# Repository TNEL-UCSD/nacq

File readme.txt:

Overview:
Design files for a electrophysiology (ephys) recording tailored for the clinic. Our system is based on Intan technologies (intantech.com). 

If any of the materials are used, please cite:

J. Hermiz, N. Rogers, E. Kaestner, M. Ganji, D. Cleary, J. Snider, D. Barba, S. Dayeh, E. Halgren, V. Gilja "A clinic compatible, open source electrophysiology system." 2016 38th Annual International Conference of the IEEE Engineering in Medicine and Biology Society (EMBC). IEEE, 2016.

Included in this system are:

-Power Isolator (nacq/pcbs/Isolation Board)
-> Provides isolated power to Intan headstages. Can support up to 256 channels.

-Easy Board (nacq/pcbs/Easy Board)
-> Adapter for isolator board to intan spi cables

-Flex Adapter (nacq/pcbs/Flex Adapter)
-> Adapter that accepts flat flex cables (FFC) and plugs into headstages (RHD2132 and RHD2164)

-NACQ Case (nacq/cases/nacq)
-> Enclosure for neural acquistion hardware (power isolator and RHD2000)

-Easy Board Case (nacq/cases/Easy Board)
-> 3D printed case

Flex Adapter Case (nacq/cases/Flex Adapter)
-> 3D printed case

Intan Headstage Cases (nacq/cases/Intan Headstages)
-> 3D printed cases for RHD2164

NACQ Software (nacq/software/nacq)
-> Software to acquire and record data. Runs only on Windows 7+ systems.

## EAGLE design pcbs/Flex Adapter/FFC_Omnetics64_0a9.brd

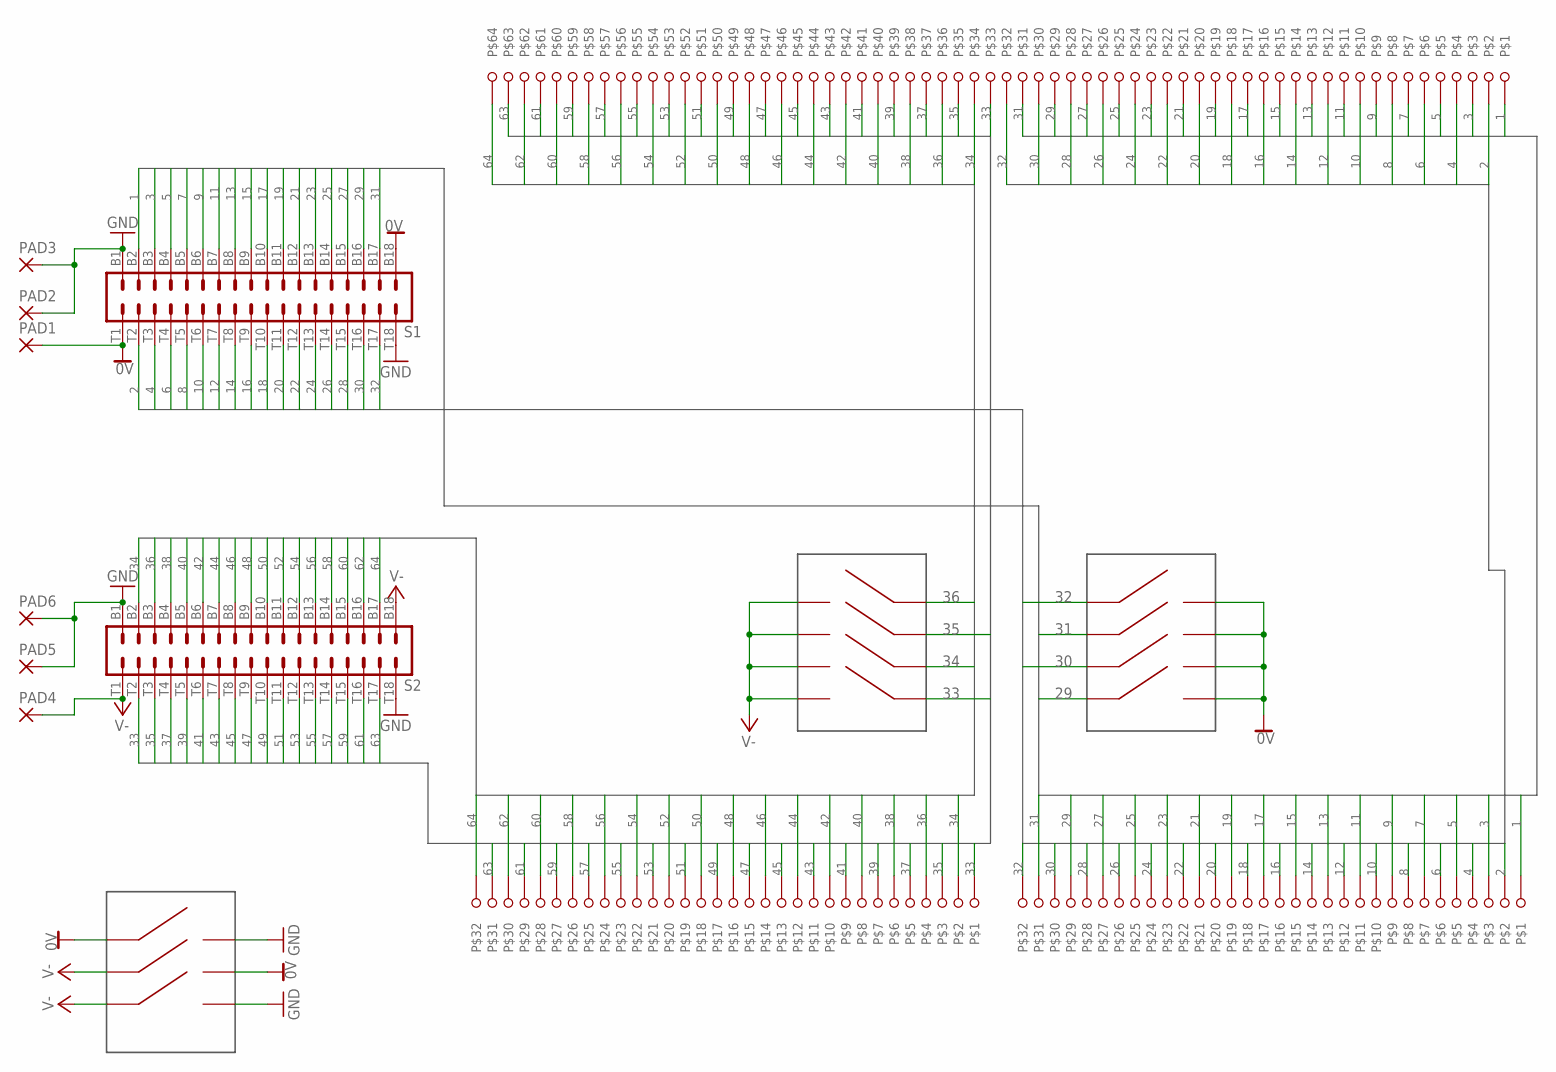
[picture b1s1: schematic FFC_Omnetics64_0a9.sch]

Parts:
PAD1, PAD2, PAD3, PAD4, PAD5, PAD6: 2,15/1,0
S1, S2: OMNETICS_A79024
U$1: OMRON64FFC-0.5MM; OMRONFFC64-0.5MM
U$2, U$3: OMRON32FFC-0.5MM; OMRON32
U$4, U$5: DIPSWITCH-4POS
U$6: DIPSWITCH-3POS

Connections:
0V: PAD1.1, S1.B18, S1.T1, U$4.P$5, U$4.P$6, U$4.P$7, U$4.P$8, U$6.P$1, U$6.P$5
1: S1.B2, U$1.P$64, U$3.P$32
2: S1.T2, U$1.P$63, U$3.P$31
3: S1.B3, U$1.P$62, U$3.P$30
4: S1.T3, U$1.P$61, U$3.P$29
5: S1.B4, U$1.P$60, U$3.P$28
6: S1.T4, U$1.P$59, U$3.P$27
7: S1.B5, U$1.P$58, U$3.P$26
8: S1.T5, U$1.P$57, U$3.P$25
9: S1.B6, U$1.P$56, U$3.P$24
10: S1.T6, U$1.P$55, U$3.P$23
11: S1.B7, U$1.P$54, U$3.P$22
12: S1.T7, U$1.P$53, U$3.P$21
13: S1.B8, U$1.P$52, U$3.P$20
14: S1.T8, U$1.P$51, U$3.P$19
15: S1.B9, U$1.P$50, U$3.P$18
16: S1.T9, U$1.P$49, U$3.P$17
17: S1.B10, U$1.P$48, U$3.P$16
18: S1.T10, U$1.P$47, U$3.P$15
19: S1.B11, U$1.P$46, U$3.P$14
20: S1.T11, U$1.P$45, U$3.P$13
21: S1.B12, U$1.P$44, U$3.P$12
22: S1.T12, U$1.P$43, U$3.P$11
23: S1.B13, U$1.P$42, U$3.P$10
24: S1.T13, U$1.P$41, U$3.P$9
25: S1.B14, U$1.P$40, U$3.P$8
26: S1.T14, U$1.P$39, U$3.P$7
27: S1.B15, U$1.P$38, U$3.P$6
28: S1.T15, U$1.P$37, U$3.P$5
29: S1.B16, U$1.P$36, U$3.P$4, U$4.P$4
30: S1.T16, U$1.P$35, U$3.P$3, U$4.P$3
31: S1.B17, U$1.P$34, U$3.P$2, U$4.P$2
32: S1.T17, U$1.P$33, U$3.P$1, U$4.P$1
33: S2.T2, U$1.P$32, U$2.P$32, U$5.P$4
34: S2.B2, U$1.P$31, U$2.P$31, U$5.P$3
35: S2.T3, U$1.P$30, U$2.P$30, U$5.P$2
36: S2.B3, U$1.P$29, U$2.P$29, U$5.P$1
37: S2.T4, U$1.P$28, U$2.P$28
38: S2.B4, U$1.P$27, U$2.P$27
39: S2.T5, U$1.P$26, U$2.P$26
40: S2.B5, U$1.P$25, U$2.P$25
41: S2.T6, U$1.P$24, U$2.P$24
42: S2.B6, U$1.P$23, U$2.P$23
43: S2.T7, U$1.P$22, U$2.P$22
44: S2.B7, U$1.P$21, U$2.P$21
45: S2.T8, U$1.P$20, U$2.P$20
46: S2.B8, U$1.P$19, U$2.P$19
47: S2.T9, U$1.P$18, U$2.P$18
48: S2.B9, U$1.P$17, U$2.P$17
49: S2.T10, U$1.P$16, U$2.P$16
50: S2.B10, U$1.P$15, U$2.P$15
51: S2.T11, U$1.P$14, U$2.P$14
52: S2.B11, U$1.P$13, U$2.P$13
53: S2.T12, U$1.P$12, U$2.P$12
54: S2.B12, U$1.P$11, U$2.P$11
55: S2.T13, U$1.P$10, U$2.P$10
56: S2.B13, U$1.P$9, U$2.P$9
57: S2.T14, U$1.P$8, U$2.P$8
58: S2.B14, U$1.P$7, U$2.P$7
59: S2.T15, U$1.P$6, U$2.P$6
60: S2.B15, U$1.P$5, U$2.P$5
61: S2.T16, U$1.P$4, U$2.P$4
62: S2.B16, U$1.P$3, U$2.P$3
63: S2.T17, U$1.P$2, U$2.P$2
64: S2.B17, U$1.P$1, U$2.P$1
GND: PAD2.1, PAD3.1, PAD5.1, PAD6.1, S1.B1, S1.T18, S2.B1, S2.T18, U$6.P$4, U$6.P$6
V-: PAD4.1, S2.B18, S2.T1, U$5.P$5, U$5.P$6, U$5.P$7, U$5.P$8, U$6.P$2, U$6.P$3

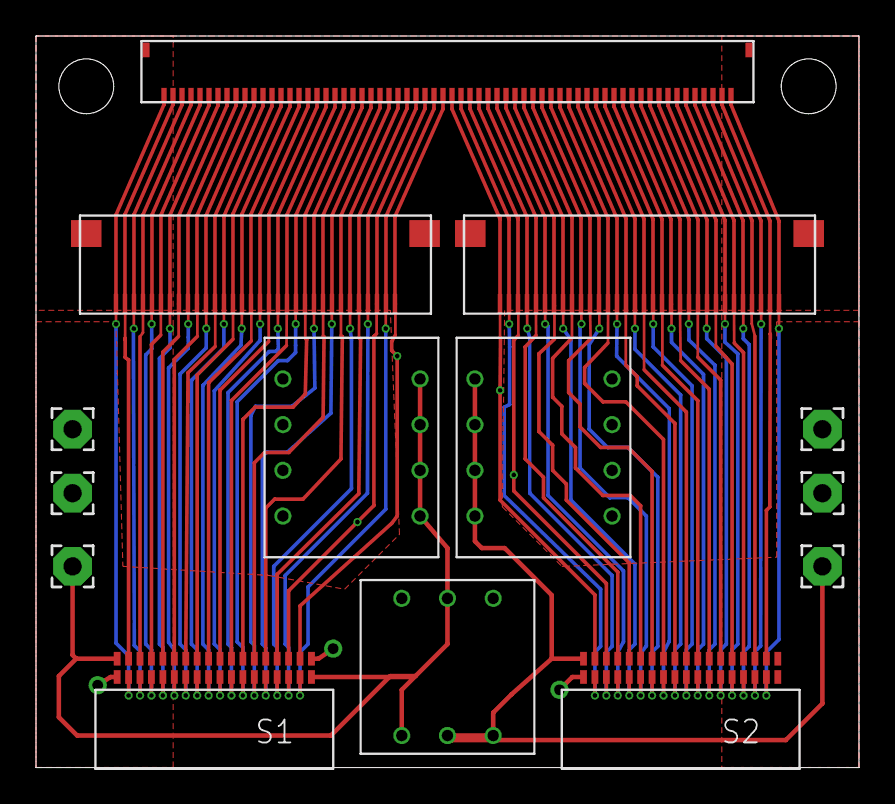
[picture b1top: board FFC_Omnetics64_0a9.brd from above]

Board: 4 copper layers, 45.7 x 40.6 mm, 14 parts (0 on the bottom side), 67 nets.

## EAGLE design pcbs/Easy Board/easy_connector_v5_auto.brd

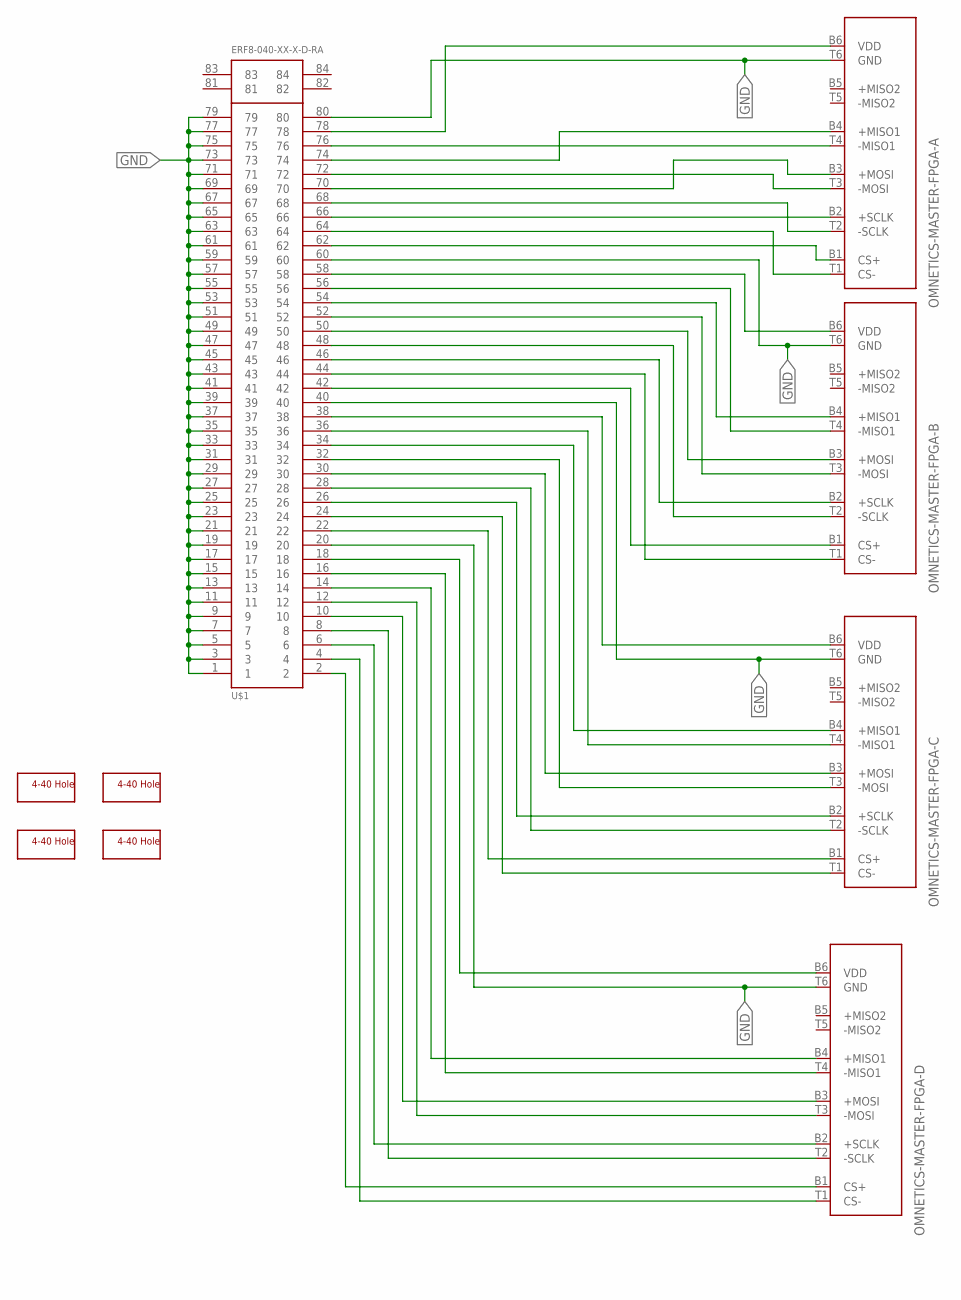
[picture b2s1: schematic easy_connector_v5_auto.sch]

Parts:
H1, H2, H3, H4: SCREW_HOLE_4-40
OMNETICS-MASTER-FPGA-A: OMNETIC-CONNECTOR; OMNETICS_PZN-12-AA-UPDATED
OMNETICS-MASTER-FPGA-B: OMNETIC-CONNECTOR; OMNETICS_PZN-12-AA-UPDATED
OMNETICS-MASTER-FPGA-C: OMNETIC-CONNECTOR; OMNETICS_PZN-12-AA-UPDATED
OMNETICS-MASTER-FPGA-D: OMNETIC-CONNECTOR; OMNETICS_PZN-12-AA-UPDATED
U$1: ERF8-040-XX-X-D-RA

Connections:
GND: OMNETICS-MASTER-FPGA-A.T6 (GND), OMNETICS-MASTER-FPGA-B.T6 (GND), OMNETICS-MASTER-FPGA-C.T6 (GND), OMNETICS-MASTER-FPGA-D.T6 (GND), U$1.1, U$1.3, U$1.5, U$1.7, U$1.9, U$1.11, U$1.13, U$1.15, U$1.17, U$1.19, U$1.20, U$1.21, U$1.23, U$1.25, U$1.27, U$1.29, U$1.31, U$1.33, U$1.35, U$1.37, U$1.39, U$1.40, U$1.41, U$1.43, U$1.45, U$1.47, U$1.49, U$1.51, U$1.53, U$1.55, U$1.57, U$1.59, U$1.60, U$1.61, U$1.63, U$1.65, U$1.67, U$1.69, U$1.71, U$1.73, U$1.75, U$1.77, U$1.79, U$1.80
MISO1_N: OMNETICS-MASTER-FPGA-A.T4 (-MISO1), U$1.76
MISO1_P: OMNETICS-MASTER-FPGA-A.B4 (+MISO1), U$1.74
unnamed: OMNETICS-MASTER-FPGA-A.T3 (-MOSI), U$1.72
unnamed: OMNETICS-MASTER-FPGA-A.B3 (+MOSI), U$1.70
unnamed: OMNETICS-MASTER-FPGA-A.T2 (-SCLK), U$1.68
unnamed: OMNETICS-MASTER-FPGA-A.B2 (+SCLK), U$1.66
unnamed: OMNETICS-MASTER-FPGA-A.T1 (CS-), U$1.64
unnamed: OMNETICS-MASTER-FPGA-A.B1 (CS+), U$1.62
unnamed: OMNETICS-MASTER-FPGA-B.T4 (-MISO1), U$1.56
unnamed: OMNETICS-MASTER-FPGA-B.B4 (+MISO1), U$1.54
unnamed: OMNETICS-MASTER-FPGA-B.T3 (-MOSI), U$1.52
unnamed: OMNETICS-MASTER-FPGA-B.B3 (+MOSI), U$1.50
unnamed: OMNETICS-MASTER-FPGA-B.T2 (-SCLK), U$1.48
unnamed: OMNETICS-MASTER-FPGA-B.B2 (+SCLK), U$1.46
unnamed: OMNETICS-MASTER-FPGA-B.T1 (CS-), U$1.44
unnamed: OMNETICS-MASTER-FPGA-B.B1 (CS+), U$1.42
unnamed: OMNETICS-MASTER-FPGA-C.T4 (-MISO1), U$1.36
unnamed: OMNETICS-MASTER-FPGA-C.B4 (+MISO1), U$1.34
unnamed: OMNETICS-MASTER-FPGA-C.T3 (-MOSI), U$1.32
unnamed: OMNETICS-MASTER-FPGA-C.B3 (+MOSI), U$1.30
unnamed: OMNETICS-MASTER-FPGA-C.T2 (-SCLK), U$1.28
unnamed: OMNETICS-MASTER-FPGA-C.B2 (+SCLK), U$1.26
unnamed: OMNETICS-MASTER-FPGA-C.T1 (CS-), U$1.24
unnamed: OMNETICS-MASTER-FPGA-C.B1 (CS+), U$1.22
unnamed: OMNETICS-MASTER-FPGA-D.T4 (-MISO1), U$1.16
unnamed: OMNETICS-MASTER-FPGA-D.B4 (+MISO1), U$1.14
unnamed: OMNETICS-MASTER-FPGA-D.T3 (-MOSI), U$1.12
unnamed: OMNETICS-MASTER-FPGA-D.B3 (+MOSI), U$1.10
unnamed: OMNETICS-MASTER-FPGA-D.T2 (-SCLK), U$1.8
unnamed: OMNETICS-MASTER-FPGA-D.B2 (+SCLK), U$1.6
unnamed: OMNETICS-MASTER-FPGA-D.T1 (CS-), U$1.4
unnamed: OMNETICS-MASTER-FPGA-D.B1 (CS+), U$1.2
VDD-A: OMNETICS-MASTER-FPGA-A.B6 (VDD), U$1.78
VDD-B: OMNETICS-MASTER-FPGA-B.B6 (VDD), U$1.58
VDD-C: OMNETICS-MASTER-FPGA-C.B6 (VDD), U$1.38
VDD-D: OMNETICS-MASTER-FPGA-D.B6 (VDD), U$1.18

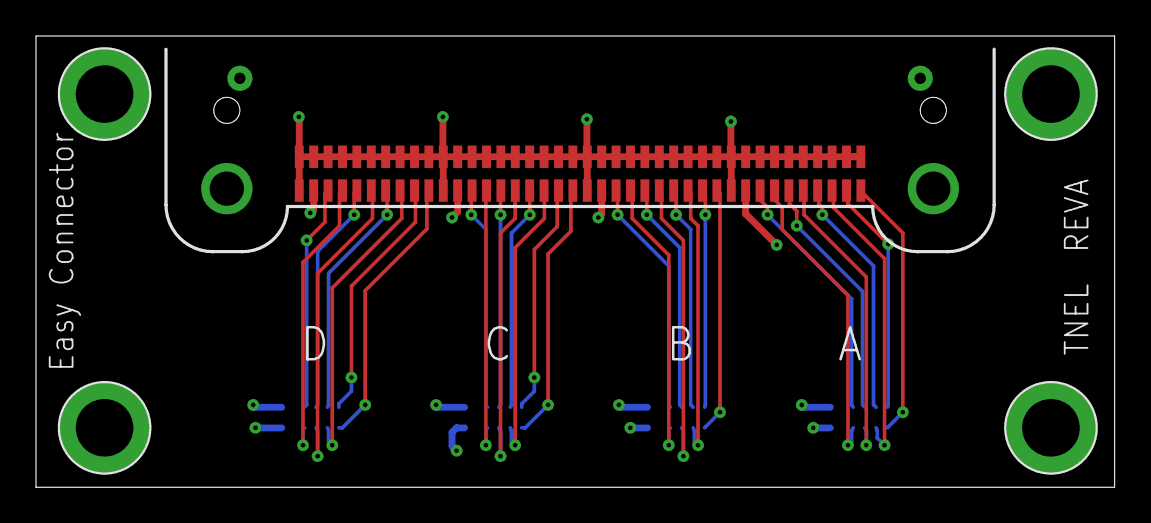
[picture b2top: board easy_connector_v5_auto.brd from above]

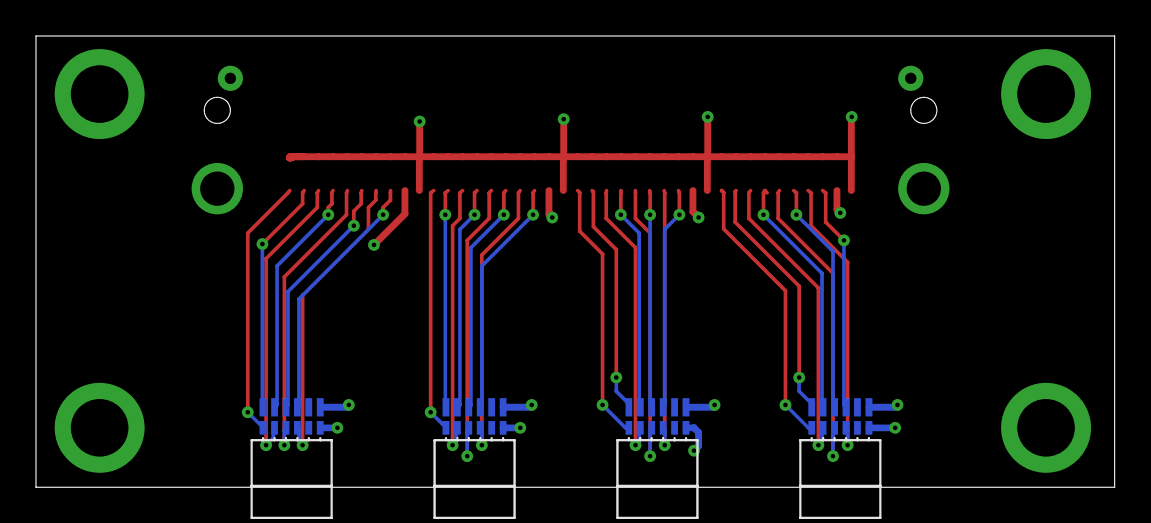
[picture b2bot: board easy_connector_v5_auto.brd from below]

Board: 4 copper layers, 59.9 x 25.1 mm, 9 parts (4 on the bottom side), 37 nets.

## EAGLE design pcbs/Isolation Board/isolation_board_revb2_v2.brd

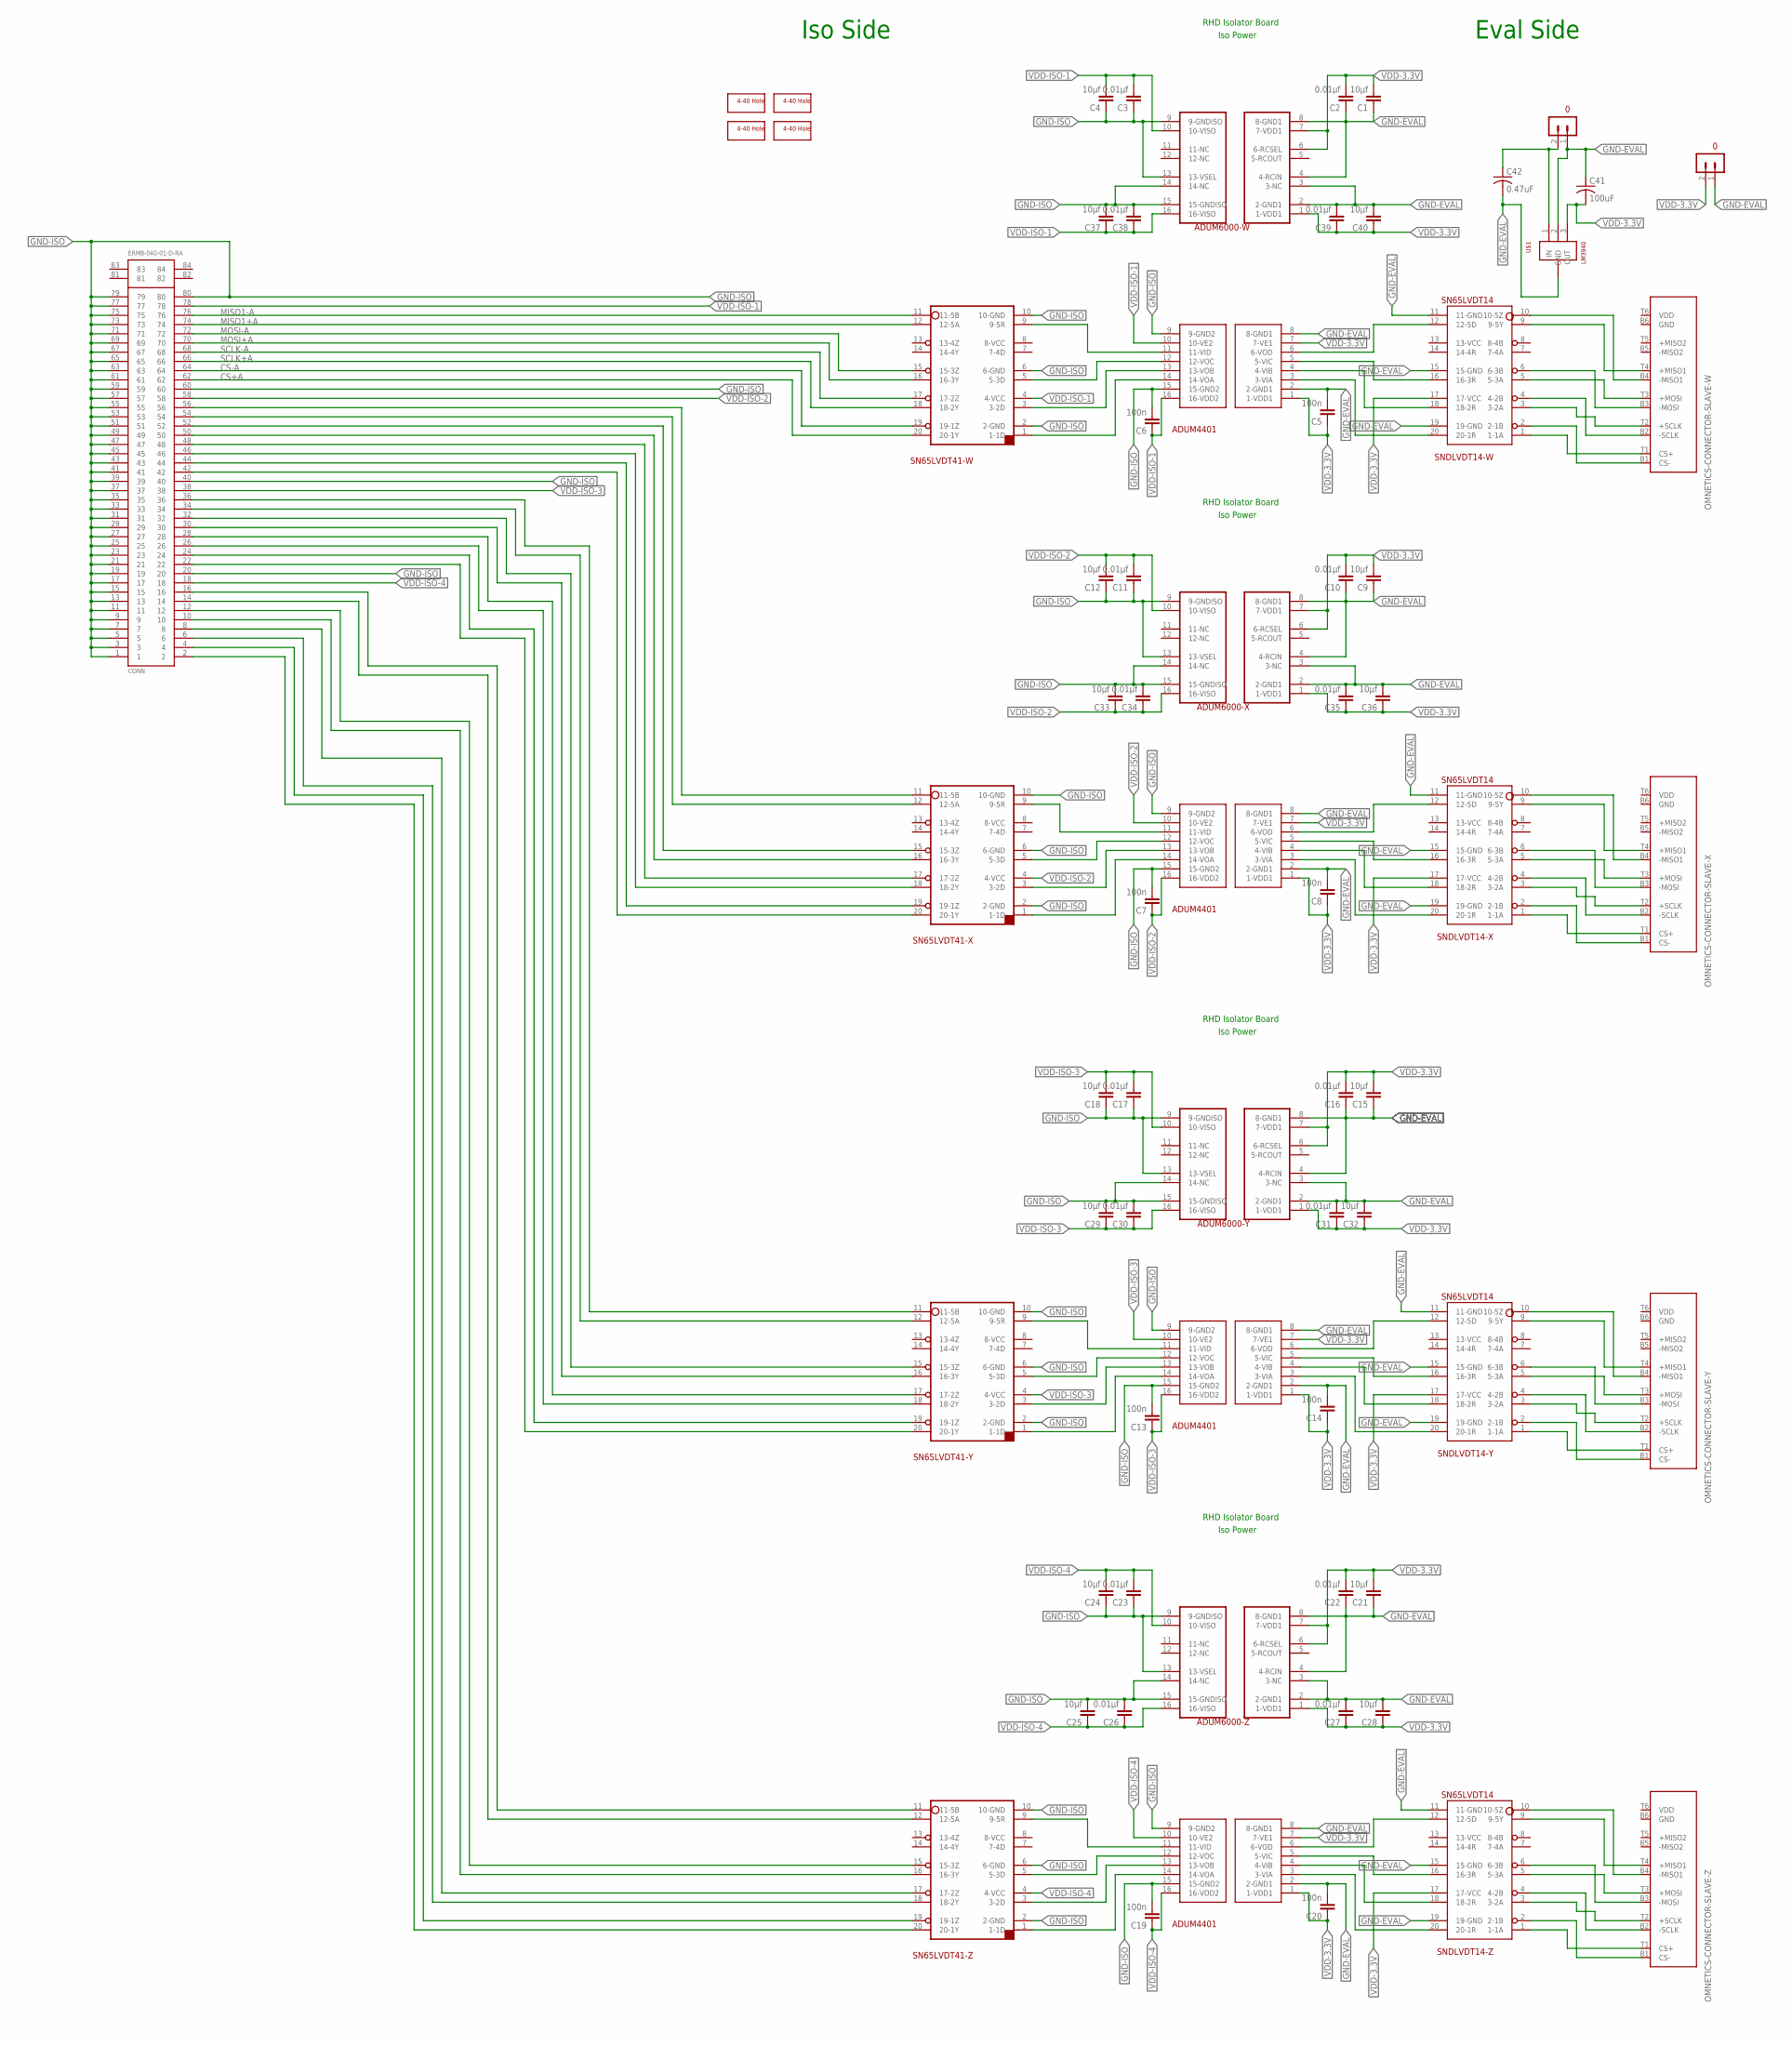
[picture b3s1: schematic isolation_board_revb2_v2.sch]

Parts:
ADUM4401-W, ADUM4401-X, ADUM4401-Y, ADUM4401-Z: ADUM4401; SOIC16R
ADUM6000-W, ADUM6000-X, ADUM6000-Y, ADUM6000-Z: ADUM6000; SOIC16R; MPN ADUM6000ARWZ
C1, C4, C9, C12, C15, C18, C21, C24, C25, C28, C29, C32, C33, C36, C37, C40: 10µf; 0805
C2, C3, C10, C11, C16, C17, C22, C23, C26, C27, C30, C31, C34, C35, C38, C39: 0.01µf; 0805
C5, C6, C7, C8, C13, C14, C19, C20: 100n; 0805
C41: 100uF; C1206
C42: 0.47uF; C0603
CONN: ERM8-040-01-D-RA
H1, H2, H3, H4: SCREW_HOLE_4-40
OMNETICS-CONNECTOR-SLAVE-W: OMNETICS-CONNECTOR-SLAVE-SIDE; OMNETICS_PZN-12-AA-UPDATED
OMNETICS-CONNECTOR-SLAVE-X: OMNETICS-CONNECTOR-SLAVE-SIDE; OMNETICS_PZN-12-AA-UPDATED
OMNETICS-CONNECTOR-SLAVE-Y: OMNETICS-CONNECTOR-SLAVE-SIDE; OMNETICS_PZN-12-AA-UPDATED
OMNETICS-CONNECTOR-SLAVE-Z: OMNETICS-CONNECTOR-SLAVE-SIDE; OMNETICS_PZN-12-AA-UPDATED
S1: TERMINAL_BLOCK_2-3.5MM-5V; TERMINAL_BLOCK_3.5MM_2_5V
S2: TERMINAL_BLOCK_2-3.5MM-3.3V; TERMINAL_BLOCK_3.5MM_2_3.3V
SN65LVDT41-W, SN65LVDT41-X, SN65LVDT41-Y, SN65LVDT41-Z: SN65LVDT41; SN65LVDT41-UPDATED
SNDLVDT14-W, SNDLVDT14-X, SNDLVDT14-Y, SNDLVDT14-Z: SN65LVDT14; SN65LDVT14
U$1: LM3940; SOT223

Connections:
CS+A: CONN.62, SN65LVDT41-W.20 (20-1Y)
CS-A: CONN.64, SN65LVDT41-W.19 (19-1Z)
GND-EVAL: ADUM4401-W.2 (2-GND1), ADUM4401-W.8 (8-GND1), ADUM4401-X.2 (2-GND1), ADUM4401-X.8 (8-GND1), ADUM4401-Y.2 (2-GND1), ADUM4401-Y.8 (8-GND1), ADUM4401-Z.2 (2-GND1), ADUM4401-Z.8 (8-GND1), ADUM6000-W.2 (2-GND1), ADUM6000-W.3 (3-NC), ADUM6000-W.4 (4-RCIN), ADUM6000-W.8 (8-GND1), ADUM6000-X.2 (2-GND1), ADUM6000-X.3 (3-NC), ADUM6000-X.4 (4-RCIN), ADUM6000-X.8 (8-GND1), ADUM6000-Y.2 (2-GND1), ADUM6000-Y.3 (3-NC), ADUM6000-Y.4 (4-RCIN), ADUM6000-Y.8 (8-GND1), ADUM6000-Z.2 (2-GND1), ADUM6000-Z.3 (3-NC), ADUM6000-Z.4 (4-RCIN), ADUM6000-Z.8 (8-GND1), C1.1, C2.1, C5.2, C8.2, C9.1, C10.1, C14.2, C15.1, C16.1, C20.2, C21.1, C22.1, C27.2, C28.2, C31.2, C32.2, C35.2, C36.2, C39.2, C40.2, C41.1, C42.2, S1.1 (0), S2.1 (0), SNDLVDT14-W.11 (11-GND), SNDLVDT14-W.15 (15-GND), SNDLVDT14-W.19 (19-GND), SNDLVDT14-X.11 (11-GND), SNDLVDT14-X.15 (15-GND), SNDLVDT14-X.19 (19-GND), SNDLVDT14-Y.11 (11-GND), SNDLVDT14-Y.15 (15-GND), SNDLVDT14-Y.19 (19-GND), SNDLVDT14-Z.11 (11-GND), SNDLVDT14-Z.15 (15-GND), SNDLVDT14-Z.19 (19-GND), U$1.2 (GND), U$1.4 (GND_T)
GND-ISO: ADUM4401-W.9 (9-GND2), ADUM4401-W.15 (15-GND2), ADUM4401-X.9 (9-GND2), ADUM4401-X.15 (15-GND2), ADUM4401-Y.9 (9-GND2), ADUM4401-Y.15 (15-GND2), ADUM4401-Z.9 (9-GND2), ADUM4401-Z.15 (15-GND2), ADUM6000-W.9 (9-GNDISO), ADUM6000-W.13 (13-VSEL), ADUM6000-W.14 (14-NC), ADUM6000-W.15 (15-GNDISO), ADUM6000-X.9 (9-GNDISO), ADUM6000-X.13 (13-VSEL), ADUM6000-X.14 (14-NC), ADUM6000-X.15 (15-GNDISO), ADUM6000-Y.9 (9-GNDISO), ADUM6000-Y.13 (13-VSEL), ADUM6000-Y.14 (14-NC), ADUM6000-Y.15 (15-GNDISO), ADUM6000-Z.9 (9-GNDISO), ADUM6000-Z.13 (13-VSEL), ADUM6000-Z.14 (14-NC), ADUM6000-Z.15 (15-GNDISO), C3.1, C4.1, C6.2, C7.2, C11.1, C12.1, C13.2, C17.1, C18.1, C19.2, C23.1, C24.1, C25.2, C26.2, C29.2, C30.2, C33.2, C34.2, C37.2, C38.2, CONN.1, CONN.3, CONN.5, CONN.7, CONN.9, CONN.11, CONN.13, CONN.15, CONN.17, CONN.19, CONN.20, CONN.21, CONN.23, CONN.25, CONN.27, CONN.29, CONN.31, CONN.33, CONN.35, CONN.37, CONN.39, CONN.40, CONN.41, CONN.43, CONN.45, CONN.47, CONN.49, CONN.51, CONN.53, CONN.55, CONN.57, CONN.59, CONN.60, CONN.61, CONN.63, CONN.65, CONN.67, CONN.69, CONN.71, CONN.73, CONN.75, CONN.77, CONN.79, CONN.80, SN65LVDT41-W.2 (2-GND), SN65LVDT41-W.6 (6-GND), SN65LVDT41-W.10 (10-GND), SN65LVDT41-X.2 (2-GND), SN65LVDT41-X.6 (6-GND), SN65LVDT41-X.10 (10-GND), SN65LVDT41-Y.2 (2-GND), SN65LVDT41-Y.6 (6-GND), SN65LVDT41-Y.10 (10-GND), SN65LVDT41-Z.2 (2-GND), SN65LVDT41-Z.6 (6-GND), SN65LVDT41-Z.10 (10-GND)
MISO1+A: CONN.74, SN65LVDT41-W.12 (12-5A)
MISO1-A: CONN.76, SN65LVDT41-W.11 (11-5B)
MOSI+A: CONN.70, SN65LVDT41-W.16 (16-3Y)
MOSI-A: CONN.72, SN65LVDT41-W.15 (15-3Z)
unnamed: ADUM4401-W.12 (12-VOC), SN65LVDT41-W.5 (5-3D)
unnamed: OMNETICS-CONNECTOR-SLAVE-W.B1 (CS-), SNDLVDT14-W.2 (2-1B)
unnamed: ADUM4401-W.11 (11-VID), SN65LVDT41-W.9 (9-5R)
unnamed: ADUM4401-W.13 (13-VOB), SN65LVDT41-W.3 (3-2D)
unnamed: ADUM4401-W.5 (5-VIC), SNDLVDT14-W.16 (16-3R)
unnamed: CONN.56, SN65LVDT41-X.11 (11-5B)
unnamed: ADUM4401-W.14 (14-VOA), SN65LVDT41-W.1 (1-1D)
unnamed: ADUM4401-W.3 (3-VIA), SNDLVDT14-W.20 (20-1R)
unnamed: ADUM4401-W.4 (4-VIB), SNDLVDT14-W.18 (18-2R)
unnamed: CONN.54, SN65LVDT41-X.12 (12-5A)
unnamed: ADUM4401-W.6 (6-VOD), SNDLVDT14-W.12 (12-5D)
unnamed: OMNETICS-CONNECTOR-SLAVE-W.T1 (CS+), SNDLVDT14-W.1 (1-1A)
unnamed: CONN.52, SN65LVDT41-X.15 (15-3Z)
unnamed: CONN.50, SN65LVDT41-X.16 (16-3Y)
unnamed: OMNETICS-CONNECTOR-SLAVE-W.T2 (+SCLK), SNDLVDT14-W.3 (3-2A)
unnamed: OMNETICS-CONNECTOR-SLAVE-W.B2 (-SCLK), SNDLVDT14-W.4 (4-2B)
unnamed: CONN.48, SN65LVDT41-X.17 (17-2Z)
unnamed: CONN.46, SN65LVDT41-X.18 (18-2Y)
unnamed: CONN.44, SN65LVDT41-X.19 (19-1Z)
unnamed: CONN.42, SN65LVDT41-X.20 (20-1Y)
unnamed: OMNETICS-CONNECTOR-SLAVE-X.T2 (+SCLK), SNDLVDT14-X.3 (3-2A)
unnamed: OMNETICS-CONNECTOR-SLAVE-X.B2 (-SCLK), SNDLVDT14-X.4 (4-2B)
unnamed: OMNETICS-CONNECTOR-SLAVE-X.T3 (+MOSI), SNDLVDT14-X.5 (5-3A)
unnamed: OMNETICS-CONNECTOR-SLAVE-X.B3 (-MOSI), SNDLVDT14-X.6 (6-3B)
unnamed: OMNETICS-CONNECTOR-SLAVE-X.T4 (+MISO1), SNDLVDT14-X.9 (9-5Y)
unnamed: OMNETICS-CONNECTOR-SLAVE-X.B4 (-MISO1), SNDLVDT14-X.10 (10-5Z)
unnamed: CONN.36, SN65LVDT41-Y.11 (11-5B)
unnamed: CONN.34, SN65LVDT41-Y.12 (12-5A)
unnamed: ADUM4401-X.14 (14-VOA), SN65LVDT41-X.1 (1-1D)
unnamed: CONN.32, SN65LVDT41-Y.15 (15-3Z)
unnamed: CONN.30, SN65LVDT41-Y.16 (16-3Y)
unnamed: ADUM4401-X.11 (11-VID), SN65LVDT41-X.9 (9-5R)
unnamed: CONN.28, SN65LVDT41-Y.17 (17-2Z)
unnamed: CONN.26, SN65LVDT41-Y.18 (18-2Y)
unnamed: C42.1, S1.2 (1), U$1.1 (IN)
unnamed: ADUM4401-X.6 (6-VOD), SNDLVDT14-X.12 (12-5D)
unnamed: OMNETICS-CONNECTOR-SLAVE-W.T3 (+MOSI), SNDLVDT14-W.5 (5-3A)
unnamed: OMNETICS-CONNECTOR-SLAVE-W.B3 (-MOSI), SNDLVDT14-W.6 (6-3B)
unnamed: OMNETICS-CONNECTOR-SLAVE-W.T4 (+MISO1), SNDLVDT14-W.9 (9-5Y)
unnamed: ADUM4401-X.5 (5-VIC), SNDLVDT14-X.16 (16-3R)
unnamed: ADUM4401-X.4 (4-VIB), SNDLVDT14-X.18 (18-2R)
unnamed: ADUM4401-X.3 (3-VIA), SNDLVDT14-X.20 (20-1R)
unnamed: OMNETICS-CONNECTOR-SLAVE-X.B1 (CS-), SNDLVDT14-X.2 (2-1B)
unnamed: OMNETICS-CONNECTOR-SLAVE-X.T1 (CS+), SNDLVDT14-X.1 (1-1A)
unnamed: ADUM4401-X.12 (12-VOC), SN65LVDT41-X.5 (5-3D)
unnamed: ADUM4401-X.13 (13-VOB), SN65LVDT41-X.3 (3-2D)
unnamed: CONN.24, SN65LVDT41-Y.19 (19-1Z)
unnamed: OMNETICS-CONNECTOR-SLAVE-W.B4 (-MISO1), SNDLVDT14-W.10 (10-5Z)
unnamed: CONN.22, SN65LVDT41-Y.20 (20-1Y)
unnamed: CONN.16, SN65LVDT41-Z.11 (11-5B)
unnamed: CONN.14, SN65LVDT41-Z.12 (12-5A)
unnamed: CONN.12, SN65LVDT41-Z.15 (15-3Z)
unnamed: CONN.10, SN65LVDT41-Z.16 (16-3Y)
unnamed: CONN.8, SN65LVDT41-Z.17 (17-2Z)
unnamed: CONN.6, SN65LVDT41-Z.18 (18-2Y)
unnamed: OMNETICS-CONNECTOR-SLAVE-Y.T2 (+SCLK), SNDLVDT14-Y.3 (3-2A)
unnamed: OMNETICS-CONNECTOR-SLAVE-Y.B2 (-SCLK), SNDLVDT14-Y.4 (4-2B)
unnamed: OMNETICS-CONNECTOR-SLAVE-Y.T3 (+MOSI), SNDLVDT14-Y.5 (5-3A)
unnamed: OMNETICS-CONNECTOR-SLAVE-Y.B3 (-MOSI), SNDLVDT14-Y.6 (6-3B)
unnamed: OMNETICS-CONNECTOR-SLAVE-Y.T4 (+MISO1), SNDLVDT14-Y.9 (9-5Y)
unnamed: OMNETICS-CONNECTOR-SLAVE-Y.B4 (-MISO1), SNDLVDT14-Y.10 (10-5Z)
unnamed: ADUM4401-Y.14 (14-VOA), SN65LVDT41-Y.1 (1-1D)
unnamed: ADUM4401-Y.11 (11-VID), SN65LVDT41-Y.9 (9-5R)
unnamed: ADUM4401-Y.6 (6-VOD), SNDLVDT14-Y.12 (12-5D)
unnamed: ADUM4401-Y.5 (5-VIC), SNDLVDT14-Y.16 (16-3R)
unnamed: ADUM4401-Y.4 (4-VIB), SNDLVDT14-Y.18 (18-2R)
unnamed: ADUM4401-Y.3 (3-VIA), SNDLVDT14-Y.20 (20-1R)
unnamed: OMNETICS-CONNECTOR-SLAVE-Y.B1 (CS-), SNDLVDT14-Y.2 (2-1B)
unnamed: OMNETICS-CONNECTOR-SLAVE-Y.T1 (CS+), SNDLVDT14-Y.1 (1-1A)
unnamed: ADUM4401-Y.12 (12-VOC), SN65LVDT41-Y.5 (5-3D)
unnamed: ADUM4401-Y.13 (13-VOB), SN65LVDT41-Y.3 (3-2D)
unnamed: CONN.4, SN65LVDT41-Z.19 (19-1Z)
unnamed: CONN.2, SN65LVDT41-Z.20 (20-1Y)
unnamed: OMNETICS-CONNECTOR-SLAVE-Z.T2 (+SCLK), SNDLVDT14-Z.3 (3-2A)
unnamed: OMNETICS-CONNECTOR-SLAVE-Z.B2 (-SCLK), SNDLVDT14-Z.4 (4-2B)
unnamed: OMNETICS-CONNECTOR-SLAVE-Z.T3 (+MOSI), SNDLVDT14-Z.5 (5-3A)
unnamed: OMNETICS-CONNECTOR-SLAVE-Z.B3 (-MOSI), SNDLVDT14-Z.6 (6-3B)
unnamed: OMNETICS-CONNECTOR-SLAVE-Z.T4 (+MISO1), SNDLVDT14-Z.9 (9-5Y)
unnamed: OMNETICS-CONNECTOR-SLAVE-Z.B4 (-MISO1), SNDLVDT14-Z.10 (10-5Z)
unnamed: ADUM4401-Z.14 (14-VOA), SN65LVDT41-Z.1 (1-1D)
unnamed: ADUM4401-Z.11 (11-VID), SN65LVDT41-Z.9 (9-5R)
unnamed: ADUM4401-Z.6 (6-VOD), SNDLVDT14-Z.12 (12-5D)
unnamed: ADUM4401-Z.5 (5-VIC), SNDLVDT14-Z.16 (16-3R)
unnamed: ADUM4401-Z.4 (4-VIB), SNDLVDT14-Z.18 (18-2R)
unnamed: ADUM4401-Z.3 (3-VIA), SNDLVDT14-Z.20 (20-1R)
unnamed: OMNETICS-CONNECTOR-SLAVE-Z.B1 (CS-), SNDLVDT14-Z.2 (2-1B)
unnamed: OMNETICS-CONNECTOR-SLAVE-Z.T1 (CS+), SNDLVDT14-Z.1 (1-1A)
unnamed: ADUM4401-Z.12 (12-VOC), SN65LVDT41-Z.5 (5-3D)
unnamed: ADUM4401-Z.13 (13-VOB), SN65LVDT41-Z.3 (3-2D)
SCLK+A: CONN.66, SN65LVDT41-W.18 (18-2Y)
SCLK-A: CONN.68, SN65LVDT41-W.17 (17-2Z)
VDD-3.3V: ADUM4401-W.1 (1-VDD1), ADUM4401-W.7 (7-VE1), ADUM4401-X.1 (1-VDD1), ADUM4401-X.7 (7-VE1), ADUM4401-Y.1 (1-VDD1), ADUM4401-Y.7 (7-VE1), ADUM4401-Z.1 (1-VDD1), ADUM4401-Z.7 (7-VE1), ADUM6000-W.1 (1-VDD1), ADUM6000-W.6 (6-RCSEL), ADUM6000-W.7 (7-VDD1), ADUM6000-X.1 (1-VDD1), ADUM6000-X.6 (6-RCSEL), ADUM6000-X.7 (7-VDD1), ADUM6000-Y.1 (1-VDD1), ADUM6000-Y.6 (6-RCSEL), ADUM6000-Y.7 (7-VDD1), ADUM6000-Z.1 (1-VDD1), ADUM6000-Z.6 (6-RCSEL), ADUM6000-Z.7 (7-VDD1), C1.2, C2.2, C5.1, C8.1, C9.2, C10.2, C14.1, C15.2, C16.2, C20.1, C21.2, C22.2, C27.1, C28.1, C31.1, C32.1, C35.1, C36.1, C39.1, C40.1, C41.2, S2.2 (1), SNDLVDT14-W.17 (17-VCC), SNDLVDT14-X.17 (17-VCC), SNDLVDT14-Y.17 (17-VCC), SNDLVDT14-Z.17 (17-VCC), U$1.3 (OUT)
VDD-ISO-1: ADUM4401-W.10 (10-VE2), ADUM4401-W.16 (16-VDD2), ADUM6000-W.10 (10-VISO), ADUM6000-W.16 (16-VISO), C3.2, C4.2, C6.1, C37.1, C38.1, CONN.78, SN65LVDT41-W.4 (4-VCC)
VDD-ISO-2: ADUM4401-X.10 (10-VE2), ADUM4401-X.16 (16-VDD2), ADUM6000-X.10 (10-VISO), ADUM6000-X.16 (16-VISO), C7.1, C11.2, C12.2, C33.1, C34.1, CONN.58, SN65LVDT41-X.4 (4-VCC)
VDD-ISO-3: ADUM4401-Y.10 (10-VE2), ADUM4401-Y.16 (16-VDD2), ADUM6000-Y.10 (10-VISO), ADUM6000-Y.16 (16-VISO), C13.1, C17.2, C18.2, C29.1, C30.1, CONN.38, SN65LVDT41-Y.4 (4-VCC)
VDD-ISO-4: ADUM4401-Z.10 (10-VE2), ADUM4401-Z.16 (16-VDD2), ADUM6000-Z.10 (10-VISO), ADUM6000-Z.16 (16-VISO), C19.1, C23.2, C24.2, C25.1, C26.1, CONN.18, SN65LVDT41-Z.4 (4-VCC)

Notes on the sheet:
RHD Isolator Board
Iso Power
Eval Side
Iso Side

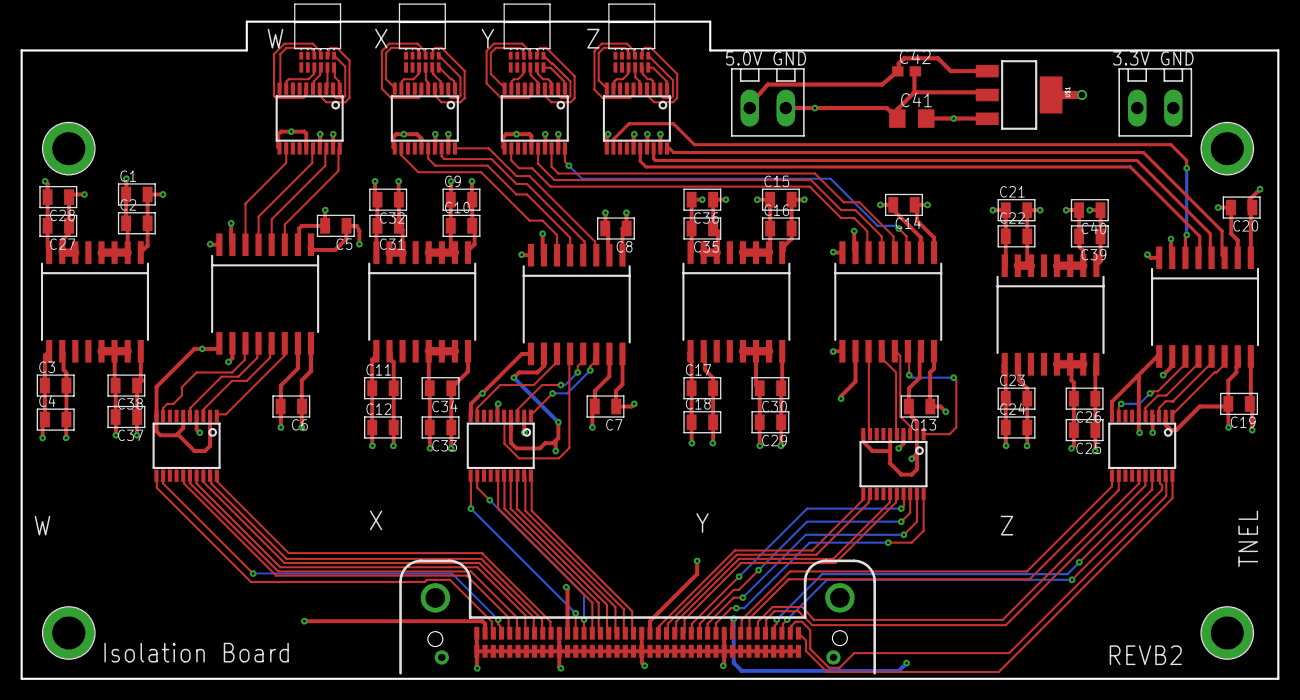
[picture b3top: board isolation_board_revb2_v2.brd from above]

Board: 4 copper layers, 121.9 x 63.8 mm, 70 parts (0 on the bottom side), 104 nets.

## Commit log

2016-03-14 Initial Commit - Includes Isolation, Easy and Flex PCBs and executable software. Coming soon source software, case design files and more documentation
2016-03-14 Readme for entire NACQ project
2016-03-16 Uploading easy board, intan headstage, and nacq enclosure design files. File format are provided in solidworks and .stl formats
2016-07-04 Moved flex adapter board design files to 'Flex Adapter' directory
2016-07-12 Included citation in readme
2016-07-17 Updated citation
2016-11-01 Uploading (1) Pigtail Adapter Case and (2) Doucmentation for Flex Adapter
2016-11-27 Updated Flex Adapter to be compatible with OSH Park and incorporated Intan's software upgrade v1.5 into system
2017-01-13 Updated Flex Adapter docs to include switch config slide
2017-04-20 Updated Flex Adapter Documentation to include full channel map
2017-12-02 Uploading ORH128 docs and files.
2017-12-19 Case for ORH128 board

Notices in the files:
parts and their libraries:
SparkFun-PowerIC: Licensing: Creative Commons ShareAlike 4.0 International - https://creativecommons.org/licenses/by-sa/4.0
